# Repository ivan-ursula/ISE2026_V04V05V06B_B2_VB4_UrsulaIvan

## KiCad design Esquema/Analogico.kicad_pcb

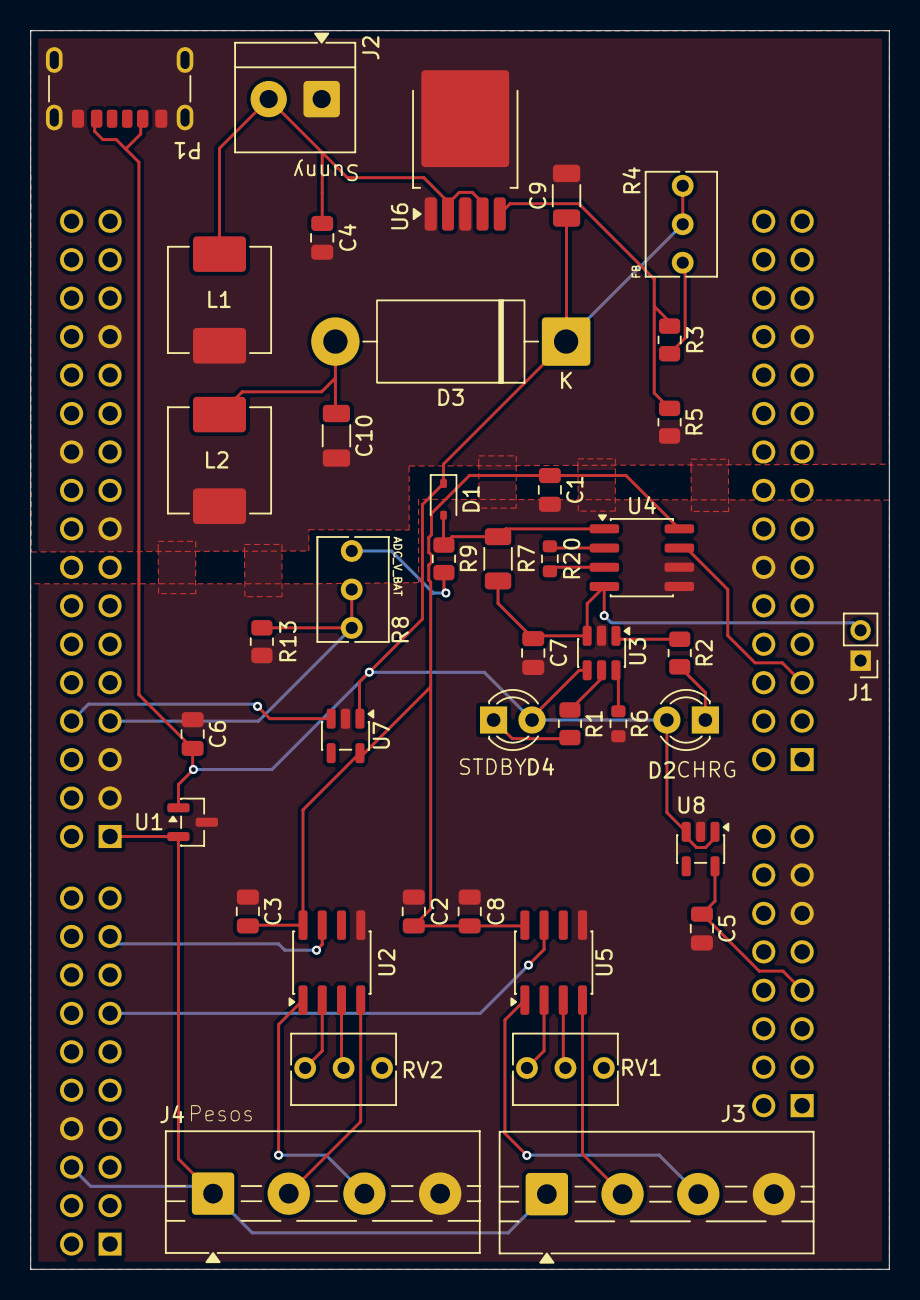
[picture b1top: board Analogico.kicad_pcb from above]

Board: 2 copper layers, 56.7 x 81.8 mm, 43 parts (0 on the bottom side), 32 nets.

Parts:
C1, C3, C8: 100nF; C_0805_2012Metric
C2, C5, C7: 10uF; C_0805_2012Metric
C4: 47uF; C_0805_2012Metric
C6: 470nF; C_0805_2012Metric
C9, C10: 220uF; C_1206_3216Metric
D1: D; D_SOD-323
D2, D4: LED; LED_D3.0mm
D3: 1N5822; D_DO-201AD_P15.24mm_Horizontal
J1: Conex_bat; PinHeader_1x02_P2.00mm_Vertical
J2: Panel Solar; TerminalBlock_4Ucon_1x02_P3.50mm_Horizontal
J3: Galga_1; TerminalBlock_MaiXu_MX126-5.0-04P_1x04_P5.00mm
J4: Galga_2; TerminalBlock_MaiXu_MX126-5.0-04P_1x04_P5.00mm
L1, L2: 33u; L_APV_APH0630
P1: USB_C_Plug_USB2.0; USB_C_Receptacle_GCT_USB4125-xx-x-0190_6P_TopMnt_Horizontal
R1, R2: 1,2k; R_0805_2012Metric
R3: 1.5k; R_0805_2012Metric
R4: 2k; Potentiometer_Bourns_3266Y_Vertical
R5: 1k; R_0805_2012Metric
R6: 2K; R_0603_1608Metric
R7: 100m; R_1206_3216Metric
R8: 1k; Potentiometer_Bourns_3266Y_Vertical
R9: 26.1k; R_0805_2012Metric
R13: 25.5k; R_0805_2012Metric
R20: 1,2K; R_0603_1608Metric
RV1, RV2: 100; Potentiometer_Bourns_3266Y_Vertical
U1: REF3020AIDBZT; SOT-23
U2, U4, U5: INA826AIDR; SOIC-8_3.9x4.9mm_P1.27mm
U3: TP4057; TSOT-23-6
U6: XL006; TO-252-5_TabPin3
U7, U8: TLV75733PDBV; SOT-23-5
U10: NUCLEO-F429ZI; MODULE_NUCLEO-F429ZI_FEMALE

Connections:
+3.3V: C5.1, U8.5 (OUT), U10.CN8_7 (+3V3_CN8)
+3.3VA: C1.1, C2.1, C3.1, C8.1, U2.8 (Vs+), U4.8 (Vs+), U5.8 (Vs+), U7.5 (OUT)
/2.048: J3.1, J4.1, U1.2 (OUT), U10.CN7_6 (AREF), U10.CN10_1 (AVDD_CN10)
/ADC_I_BAT: U4.7, U10.CN9_5 (A2/ADC123_IN13)
/ADC_PESO_1: U5.7, U10.CN7_13 (D22/I2S_B_SD/SPI_B_MOSI)
/ADC_PESO_2: U2.7, U10.CN7_17 (D24/SPI_B_NSS)
/ADC_V_BAT: R8.2, R8.3, R13.1, U10.CN10_7 (A6/ADC_A_IN)
/EN: U7.3 (EN), U10.CN10_8 (D4/IO)
/FB: R3.2, R5.1, U6.5 (FB)
GND: C1.2, C2.2, C3.2, C4.2, C5.2, C6.2, C7.2, C8.2, C9.2, C10.1, J1.1, J2.1, J3.4, J4.4, L1.2, L2.1, P1.A12 (GND), P1.B12 (GND), P1.S1 (SHIELD), R5.2, R6.2, R13.2, U1.3 (GND), U2.5 (Vs-), U3.2 (GND), U4.5 (Vs-), U4.6 (Ref), U5.5 (Vs-), U6.1 (GND), U6.3 (SW), U7.2 (GND), U8.2 (GND), U10.CN7_8 (GND_CN7), U10.CN8_11 (GND_CN8), U10.CN8_13 (GND_CN8), U10.CN9_12 (GND_CN9), U10.CN9_23 (GND_CN9), U10.CN10_3 (AGND_CN10), U10.CN10_5 (GND_CN10), U10.CN10_17 (GND_CN10), U10.CN10_22 (GND_CN10), U10.CN10_27 (GND_CN10)
unnamed: D1.2 (A), R7.2, R9.1, U4.1 (-)
unnamed: C6.1, C9.1, D1.1 (K), D2.2 (A), D3.1 (K), D4.2 (A), P1.A9 (VBUS), P1.B9 (VBUS), R4.2, R4.3, U1.1 (IN), U3.4 (V_{CC}), U7.1 (IN), U8.1 (IN), U8.3 (EN)
unnamed: D2.1 (K), R2.1
unnamed: C10.2, D3.2 (A), L2.2
unnamed: D4.1 (K), R1.1
unnamed: C7.1, J1.2, R7.1, U3.3 (BAT), U4.4 (+)
unnamed: C4.1, J2.2, L1.1, U6.2 (EN), U6.4 (VIN)
unnamed: J3.2, U5.4 (+)
unnamed: J3.3, U5.1 (-)
unnamed: J4.2, U2.4 (+)
unnamed: J4.3, U2.1 (-)
unnamed: R3.1, R4.1
unnamed: R8.1, R9.2
unnamed: R20.1, U4.3 (Rg)
unnamed: R20.2, U4.2 (Rg)
unnamed: RV1.2, U5.3 (Rg)
unnamed: RV1.3, U5.2 (Rg)
unnamed: RV2.2, U2.3 (Rg)
unnamed: RV2.3, U2.2 (Rg)
unnamed: R6.1, U3.6 (PROG)
unnamed: R1.2, U3.5 (STDBY)
unnamed: R2.2, U3.1 (~CHRG)

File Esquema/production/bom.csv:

Designator,Footprint,Quantity,Value,LCSC Part #
"C1, C3, C8",0805,3,100nF,C476766
"C10, C9",1206,2,220uF,C412252
"C2, C5, C7",0805,3,10uF,C15850
C4,0805,1,47uF,C16780
C6,0805,1,470nF,C16780
D1,D_SOD-323,1,D,C146335
"D2, D4",LED_D3.0mm,2,LED,C85161
D3,D_DO-201AD_P15.24mm_Horizontal,1,1N5822,C2476
J1,PinHeader_1x02_P2.00mm_Vertical,1,Conex_bat,C157932
J2,TerminalBlock_4Ucon_1x02_P3.50mm_Horizontal,1,Panel Solar,C695629
J3,TerminalBlock_MaiXu_MX126-5.0-04P_1x04_P5.00mm,1,Galga_1,C192769
J4,TerminalBlock_MaiXu_MX126-5.0-04P_1x04_P5.00mm,1,Galga_2,C192769
"L1, L2",L_APV_APH0630,2,33u,C5349704
P1,USB_C_Receptacle_GCT_USB4125-xx-x-0190_6P_TopMnt_Horizontal,1,USB_C_Plug_USB2.0,C2927028
"R1, R2",0805,2,"1,2k",C114526
R13,0805,1,25.5k,C17414
R20,0603,1,"1,2K",C445629
R3,0805,1,1.5k,C114555
R4,Potentiometer_Bourns_3266Y_Vertical,1,2k,C48997938
R5,0805,1,1k,
R6,0603,1,2K,C22975
R7,1206,1,100m,C25334
R8,Potentiometer_Bourns_3266Y_Vertical,1,1k,C48997938
R9,0805,1,26.1k,C2933386
"RV1, RV2",Potentiometer_Bourns_3266Y_Vertical,2,100,C48997939
U1,SOT-23,1,REF3020AIDBZT,C2877902
U10,MODULE_NUCLEO-F429ZI_FEMALE,1,NUCLEO-F429ZI,
"U2, U4, U5",SOIC-8_3.9x4.9mm_P1.27mm,3,INA826AIDR,C38433
U3,TSOT-23-6,1,TP4057,C725791
U6,TO-252-5_TabPin3,1,XL006,C73012
"U7, U8",SOT-23-5,2,TLV75733PDBV,C485517

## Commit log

2026-03-27 añado esquema y carpetas
2026-03-29 Cambios en el esquematico del viernes
2026-03-29 He añadido los correspondientes datasheets y he corregido un componente que estaba mal colocado.
2026-03-30 He añadido la footprint y simbolo del stm32f429zi
2026-03-30 Añado, ahora si, el simbolo y huella del micro
2026-04-09 Huellas y componentes ya asignados
2026-04-10 PCB 1.0
2026-04-10 configuracion e interrupcion del NFC
2026-04-10 PCB ver. 1.1 Signed-off-by: ricardo.socorro <ricardo.socorro@alumnos.upm.es>
2026-04-12 Placa ya terminada
2026-04-14 añado modulo uart
2026-04-14 Uart ricardo
2026-04-14 uart hecho bien
2026-04-14 uart por fa
2026-04-14 uart ordenado y pido disculpas
2026-04-14 modulo sd
2026-04-17 nfc funcional falta cola mensaje
2026-04-17 nfc funcional falta cola msg
2026-04-17 Pagina web, falta aplicar a los links
2026-04-17 SD configurando el ffconfig para usar la librería
2026-04-18 SD con el fileSystem de keil
2026-04-20 lectura y escritura de sensor presencia
2026-04-20 interrupcion medio hecha
2026-04-22 SD ya funcionando :D
2026-04-22 Ya funciona la SD :'D
2026-04-24 Página vertical con diseño completo, ahora alertas
2026-04-24 Empezando el módulo de la SD para nuestro proyecto
2026-04-24 Edición de la SD
2026-04-28 vhcl sin interrupcion
2026-04-29 Sensor de presencia funcionando (ahora sí)
2026-04-29 ordenado segun ivan
2026-05-02 introduzco cola de mensajes
2026-05-02 empiezo integracion de la taquilla
2026-05-02 envia por uart uid de tarjetas
2026-05-04 integracion del rtc y comandos
2026-05-05 integro adc para estado activo
2026-05-06 adc funcional
2026-05-06 Cambios en los comandos
2026-05-06 Cambios en sleep.c
2026-05-08 Cambios en la integracion de la taquilla
2026-05-09 comando lecturas
2026-05-11 añado el modo stop
2026-05-11 stop mode
2026-05-11 stop mode sin revivir
2026-05-11 Cambios en el handler de la interrupción
2026-05-12 inicio timer de pedida de hora
2026-05-13 calibracoin de los adc
2026-05-13 configuracion correcta de keil
2026-05-13 Comandos
2026-05-13 nfc y adc pines cambiados
2026-05-13 comando corriente tension peso
2026-05-13 integracion bajo consumo a medias
2026-05-13 Módulo página completo
2026-05-14 Pagina implementando el COM
2026-05-15 cambios en la taquilla
2026-05-15 cambios en el bajo consumo
2026-05-16 Falta enviar hora en el COM
2026-05-16 Arreglado el bajo consumo
2026-05-16 Poniendo el RTC
2026-05-16 Funciones para mandar a dormir y despertar
2026-05-16 cambios en el principal
2026-05-17 Funciona el RTC
2026-05-17 Callbacks de las alarmas del RTC
2026-05-17 Problema con la alarma B
2026-05-17 Ya funciona el RTC
2026-05-17 Web con el com terminada
2026-05-17 Cambios para la app final
2026-05-17 Actualizado cambio de texto
2026-05-17 Todo
2026-06-04 Cambio en el modulo de recepcion de usart
2026-06-04 Modulo pwm hecho. El codigo cambia la frecuencia de la señal pwm y la mantiene en un rendimiento del 50%
2026-06-12 Actualizado
2026-06-15 Cambios del finde
2026-06-16 Cambios martes 16
2026-06-16 Cambio en las alarmas de despertar y dormir. Implementacion del zumbador y los leds
2026-06-16 martes por la tarde
2026-06-16 Cambios en el principal y en el adc
2026-06-17 Cambios en sleep y principal
2026-06-17 Implementacion del zumbador
2026-06-17 Cambios en principal
2026-06-17 99% finalizado falta revisar sd usuarios
2026-06-17 El proyecto está al 99%
    (te odio sensor de presencia)
2026-06-19 Terminado a falta de limpiar código
2026-06-19 final
2026-06-19 FUNCIONAAAAAAAAAAAAAAAA
2026-06-19 FUNCIONAAAAAAAAAAA
2026-06-20 Código limpio y con comentarios
2026-06-20 Update sd.c quitando comentarios
2026-06-21 Pines del USART estaban mal puestos
2026-06-21 Clean target
